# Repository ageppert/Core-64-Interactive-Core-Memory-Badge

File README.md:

# Core-64-Interactive-Core-Memory-Badge
Weave your own 64 bits of core memory over the top of LEDs to interact with directly using a magnetic wand.

Purchase: https://www.Core64.io

Follow this project at: https://hackaday.io/project/166155-core-64-interactive-core-memory-badge

You are in the development repository. Beta Kits and production version firmware is at https://github.com/ageppert/Core64/

# Hardware Version History (latest on top)

v0.5 Triple Board (added custom LED Matrix) - Beta Test Kits. Beta Kit Repo at https://github.com/ageppert/Core64/

v0.4 Core Board - Neon Pixel Edition. Expanded Core Grid Array to work with [Neon Pixels](https://pierremuth.wordpress.com/2020/07/08/neon-pixel/)!

v0.4 Dual Boards (Blue LB + Yellow CB), moved up to Teensy 3.2, removed IO Expanders, added more expansion/hacking headers.

v0.3.1 Hand re-worked v0.3 with 5V0 and 3V3 regulators each seperately sourced after power switch to provide improved power supplies.

v0.3 Dual Boards (both Red) with Teensy LC. One core board, one logic board. Used IO Expanders to drive the Core matrix, which ended up being way too slow.

v0.2 Bug fixes learned from v0.1 applied. This version has not been made or tested, but should work.

v0.1.1 Single Green Board worked after I added missing OR gate circuitry!

v0.1 Single Green Board with Teensy LC. The first hand assembled prototype. Made one and it worked after I added missing circuitry!

Share-A-Hack version

Proof-Of-Concept version

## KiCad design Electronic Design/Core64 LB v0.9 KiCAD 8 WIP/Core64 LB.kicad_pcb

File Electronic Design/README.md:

# Electronic Design

Datasheets

Native KiCad files for the schematic and PCB. (KiCad Version: (5.1.2-1)-1, release build)

Teensy LC Pin Usage Mapping

BOM

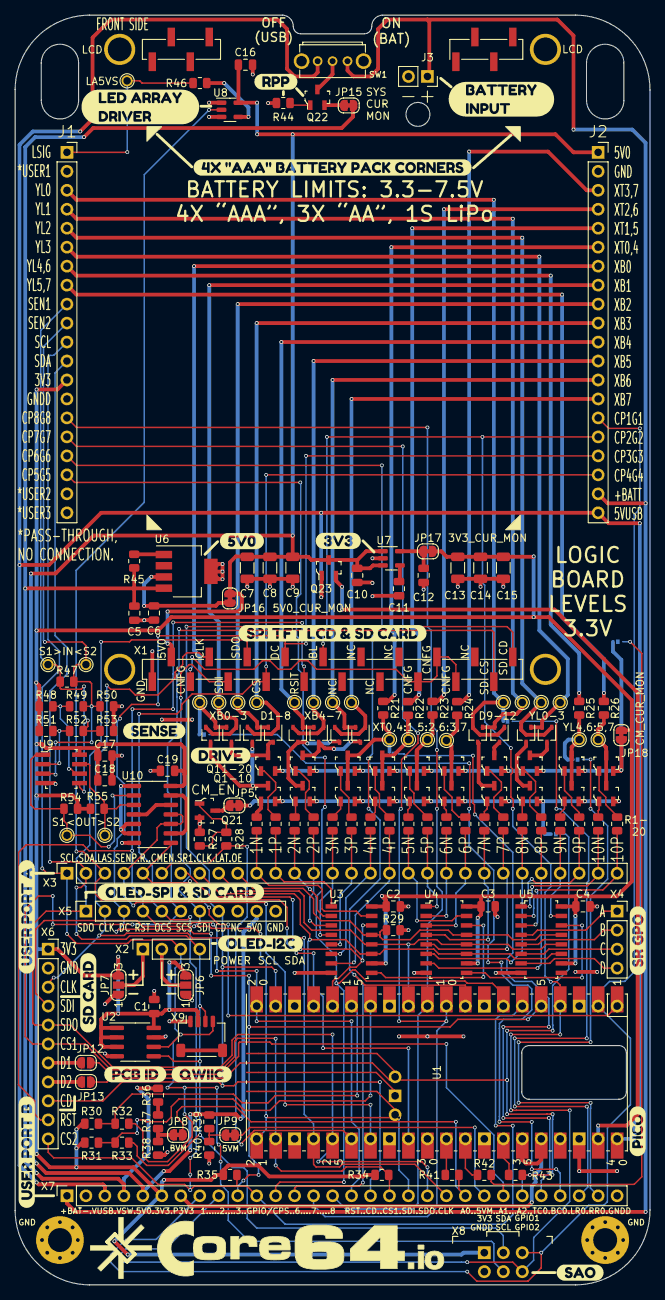
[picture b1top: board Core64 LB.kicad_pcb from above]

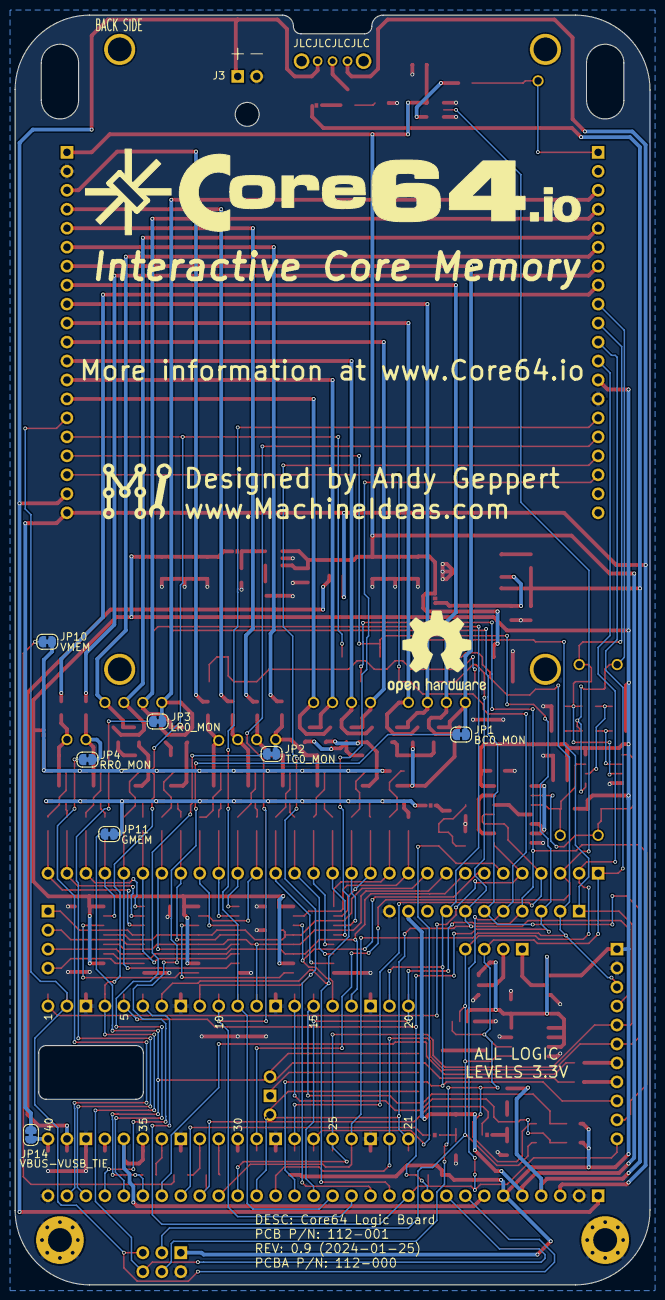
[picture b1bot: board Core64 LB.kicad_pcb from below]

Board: 2 copper layers, 85.0 x 170.0 mm, 198 parts (10 on the bottom side), 154 nets.

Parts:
C1, C2, C3, C4, C16, C17, C19: 0.1uF; C_0805_2012Metric
C5, C6, C10, C12: 1uF; C_0805_2012Metric
C7, C8, C9, C13, C14, C15: 220uF; C_1206_3216Metric
C11: 0.01uF; C_0805_2012Metric
C18: 10uF; C_0805_2012Metric
D1, D3, D5, D7, D9, D11: BAT54CW; SOT-323_SC-70
D2, D4, D6, D8, D10, D12: BAT54AW; SOT-323_SC-70
H1, H2: GND PAD; MountingHole_3.2mm_M3_Pad_Via
J1, J2: SSW-116-22-F-S-VS‎; PinSocket_1x20_P2.54mm_Vertical
J3: ALT. BATT.; PinSocket_1x02_P2.54mm_Vertical
JP1: BC0_MON; SolderJumper-2_P1.3mm_Bridged_RoundedPad1.0x1.5mm
JP2: TC0_MON; SolderJumper-2_P1.3mm_Bridged_RoundedPad1.0x1.5mm
JP3: LR0_MON; SolderJumper-2_P1.3mm_Bridged_RoundedPad1.0x1.5mm
JP4: RR0_MON; SolderJumper-2_P1.3mm_Bridged_RoundedPad1.0x1.5mm
JP5, JP11: GMEM; SolderJumper-2_P1.3mm_Bridged_RoundedPad1.0x1.5mm
JP6, JP7: SolderJumper_3_Open; SolderJumper-3_P1.3mm_Open_RoundedPad1.0x1.5mm_NumberLabels
JP8: BAT_MON; SolderJumper-2_P1.3mm_Bridged_RoundedPad1.0x1.5mm
JP9: 5V0_MON; SolderJumper-2_P1.3mm_Bridged_RoundedPad1.0x1.5mm
JP10: VMEM; SolderJumper-2_P1.3mm_Bridged_RoundedPad1.0x1.5mm
JP12: D1; SolderJumper-2_P1.3mm_Open_RoundedPad1.0x1.5mm
JP13: D2; SolderJumper-2_P1.3mm_Open_RoundedPad1.0x1.5mm
JP14: VBUS_VUSB_TIE; SolderJumper-2_P1.3mm_Bridged_RoundedPad1.0x1.5mm
JP15: SYS_CUR_MON; SolderJumper-2_P1.3mm_Bridged_RoundedPad1.0x1.5mm
JP16: 5V0_CUR_MON; SolderJumper-2_P1.3mm_Bridged_RoundedPad1.0x1.5mm
JP17: 3V3_CUR_MON; SolderJumper-2_P1.3mm_Bridged_RoundedPad1.0x1.5mm
JP18: CM_CUR_MON; SolderJumper-2_P1.3mm_Bridged_RoundedPad1.0x1.5mm
L1: Core_64_Logo; Core64.io_w_core_symbol
L1#2: Core_64_Logo; Machine_Ideas_logo_1
L2: Core_64_Logo; Core64.io_w_core_symbol2
L4: Logo_Open_Hardware_Small; OSHW-Logo2_14.6x12mm_SilkScreen
Q1, Q2, Q3, Q4, Q5, Q6, Q7, Q8, Q9, Q10: MMBT4401LT1G; SOT-23-3
Q11, Q12, Q13, Q14, Q15, Q16, Q17, Q18, Q19, Q20: MMBT4403LT1G; SOT-23-3
Q21: NVTR4503NT1G_NMOS_GSD; SOT-23-3
Q22, Q23: SL3401A; SOT-23-3
R1, R2, R3, R4, R5, R6, R7, R8, R9, R10, R11, R12, R13, R14, R15, R16, R17, R18, R19, R20, R28, R46: 470; R_0805_2012Metric
R21, R22, R23, R24, R25, R26: 6R8-5%; R_0805_2012Metric
R27, R29, R34, R35, R36, R37, R38, R39, R40, R44, R45: 10k; R_0805_2012Metric
R30, R31, R54, R55: 1K2; R_0805_2012Metric
R32, R33: 68; R_0805_2012Metric
R41, R42, R43: 1k2; R_0805_2012Metric
R47, R50, R53: 1K5-1%; R_0805_2012Metric
R48, R51: 1K8-1%; R_0805_2012Metric
R49, R52: 11-1%; R_0805_2012Metric
SW1: SK12D07L4B; SK12D07VG4
TP1: XB0; TestPoint_THTPad_D1.5mm_Drill1.0mm
TP2: XB1; TestPoint_THTPad_D1.5mm_Drill1.0mm
TP3: XB2; TestPoint_THTPad_D1.5mm_Drill1.0mm
TP4: XB3; TestPoint_THTPad_D1.5mm_Drill1.0mm
TP5: XB4; TestPoint_THTPad_D1.5mm_Drill1.0mm
TP6: XB5; TestPoint_THTPad_D1.5mm_Drill1.0mm
TP7: XB6; TestPoint_THTPad_D1.5mm_Drill1.0mm
TP8: XB7; TestPoint_THTPad_D1.5mm_Drill1.0mm
TP9: XT0,4; TestPoint_THTPad_D1.5mm_Drill1.0mm
TP10: XT1,5; TestPoint_THTPad_D1.5mm_Drill1.0mm
TP11: XT2,6; TestPoint_THTPad_D1.5mm_Drill1.0mm
TP12: XT3,7; TestPoint_THTPad_D1.5mm_Drill1.0mm
TP13: YL1; TestPoint_THTPad_D1.5mm_Drill1.0mm
TP14: YL0; TestPoint_THTPad_D1.5mm_Drill1.0mm
TP15: YL3; TestPoint_THTPad_D1.5mm_Drill1.0mm
TP16: YL2; TestPoint_THTPad_D1.5mm_Drill1.0mm
TP17: YL4,6; TestPoint_THTPad_D1.5mm_Drill1.0mm
TP18: YL5,7; TestPoint_THTPad_D1.5mm_Drill1.0mm
TP19: LA5VS; TestPoint_THTPad_D1.5mm_Drill1.0mm
TP20: S1 IN; TestPoint_THTPad_D1.5mm_Drill1.0mm
TP21: S2 IN; TestPoint_THTPad_D1.5mm_Drill1.0mm
TP22: S2 OUT; TestPoint_THTPad_D1.5mm_Drill1.0mm
TP23: S1 OUT; TestPoint_THTPad_D1.5mm_Drill1.0mm
U1: PICO; RPi_PicoW_SMD_TH_Abg
U2: M24C02-RMN; SOIC-8_3.9x4.9mm_P1.27mm
U3, U4, U5: 74HC595D; SOIC-16_W3.90mm
U6: LP38693MP-5.0; SOT-223-5
U7: SSP9193-33M5R; SOT-23-5
U8: SN74LV1T125DBVR; SOT-23-5
U9: LM393; SOIC-8_W3.9mm
U10: SN74HC02DR; SOIC-14_3.9x8.7mm_P1.27mm
X1: Adafruit_3.2_TFT_1743; Adafruit_3.2_TFT_Dual_PinHeader_1x20_P2.54mm_Vertical_SMD_P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
X2: SSW-104-22-L-S-VS; PinSocket_1x04_P2.54mm_Vertical
X3, X7: TBD; PinSocket_1x30_P2.54mm_Vertical
X4: CA_SR_GPO_ABCD; PinSocket_1x04_P2.54mm_Vertical
X5: HEADER_11-PIN_0.1; PinSocket_1x11_P2.54mm_Vertical
X6: Header_11-PIN_0.1; PinSocket_1x11_P2.54mm_Vertical
X8: SAO_conn_SFH11-NBPC-D03-ST-BK; Badgelife-SAOv169-BADGE-2x3
X9: QWIIC; JST_SH_SM04B-SRSS-TB_1x04-1MP_P1.00mm_Horizontal
kibuzzard-6417AF30: G***; kibuzzard-6417AF30
kibuzzard-6417CDFD: G***; kibuzzard-6417CDFD
kibuzzard-6417CE14: G***; kibuzzard-6417CE14
kibuzzard-64178C85: G***; kibuzzard-64178C85
kibuzzard-64178DD4: G***; kibuzzard-64178DD4
kibuzzard-64178DE8: G***; kibuzzard-64178DE8
kibuzzard-64178DF4: G***; kibuzzard-64178DF4
kibuzzard-64178E2E: G***; kibuzzard-64178E2E
kibuzzard-64178E4F: G***; kibuzzard-64178E4F
kibuzzard-64178E7C: G***; kibuzzard-64178E7C
kibuzzard-64178E9B: G***; kibuzzard-64178E9B
kibuzzard-64178E12: G***; kibuzzard-64178E12
kibuzzard-64178E45: G***; kibuzzard-64178E45
kibuzzard-64178E73: G***; kibuzzard-64178E73
kibuzzard-64178E92: G***; kibuzzard-64178E92
kibuzzard-64178EA5: G***; kibuzzard-64178EA5
kibuzzard-64179D69: G***; kibuzzard-64179D69
kibuzzard-64179D78: G***; kibuzzard-64179D78
kibuzzard-64179E5D: G***; kibuzzard-64179E5D

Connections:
3V3: C1.1, C2.1, C3.1, C4.1, C13.1, C14.1, C15.1, C17.1, C18.1, C19.1, J1.13, JP6.3 (B), JP7.3 (B), JP17.2 (B), JP18.1 (A), R30.1, R31.1, R34.1, R35.2, R48.1, R51.1, R54.1, R55.1, U2.1 (E0), U2.2 (E1), U2.3 (E2), U2.8 (VCC), U3.10 (~SRCLR), U3.16 (VCC), U4.10 (~SRCLR), U4.16 (VCC), U5.10 (~SRCLR), U5.16 (VCC), U9.8 (V+), U10.14 (VCC), X6.1, X7.6, X8.1 (3V3), X9.2
5V0: C7.1, C8.1, C9.1, C10.1, C16.1, J2.1, JP16.2 (B), Q23.3 (D), R39.1, U7.1 (IN), U7.3 (EN), U8.5 (VCC), X1.2 (3-5V), X5.10, X7.5
5VUSB: J2.20, JP14.2 (B), Q23.1 (G), SW1.3 (C), X7.3
+BATT: J2.19, J3.1, SW1.1 (A), X7.1
+VSW: C5.1, JP15.2 (B), R36.2, R45.1, U6.4 (IN), X7.4
-BATT: C1.2, C2.2, C3.2, C4.2, C5.2, C6.2, C7.2, C8.2, C9.2, C10.2, C11.2, C12.2, C13.2, C14.2, C15.2, C16.2, C17.2, C18.2, C19.2, H1.1, H2.1, J1.14, J2.2, J3.2, JP6.1 (A), JP7.1 (A), Q21.2 (S), R27.1, R29.1, R38.2, R40.2, R44.2, R50.2, R53.2, U1.3 (GND), U1.8 (GND), U1.13 (GND), U1.18 (GND), U1.23 (GND), U1.28 (GND), U1.33 (AGND/GND), U1.38 (GND), U2.4 (VSS), U2.7 (~WC), U3.8 (GND), U4.8 (GND), U5.8 (GND), U6.5 (GND), U7.2 (GND), U8.1 (/OE), U8.3 (GND), U9.4 (V-), U10.7 (GND), X1.1 (GND), X5.11, X6.2, X7.2, X7.30, X8.2 (GND), X9.1
/ADC0: R41.1, U1.31 (I2C1_SDA/ADC0/GP26)
/ADC0_BUFF: JP8.2 (B), R41.2, X7.22
/ADC1: R42.1, U1.32 (I2C1_SCL/ADC1/GP27)
/ADC1_BUFF: JP10.1 (A), JP12.2 (B), R42.2, X7.24
/ADC2: R43.1, U1.34 (ADC2/GP28)
/ADC2_BUFF: JP11.1 (A), JP13.2 (B), R43.2, X7.25
/CA_SENSE_1_OUT: R55.2, TP23.1, U9.7, U10.3
/CA_SENSE_2_OUT: R54.2, TP22.1, U9.1, U10.2
/CA_SR_GPO_A: U5.4 (QE), X4.1
/CA_SR_GPO_B: U5.5 (QF), X4.2
/CA_SR_GPO_C: U5.6 (QG), X4.3
/CA_SR_GPO_D: U5.7 (QH), X4.4
/CA_SR_SER2: U3.9 (QH'), U4.14 (SER)
/CA_SR_SER3: U4.9 (QH'), U5.14 (SER)
/CM_EN: R28.1, U1.26 (I2C0_SDA/GP20), X3.6
/CM_Q1N: R1.2, U3.15 (QA), X3.11
/CM_Q1P: R2.2, U3.1 (QB), X3.12
/CM_Q2N: R3.2, U3.2 (QC), X3.13
/CM_Q2P: R4.2, U3.3 (QD), X3.14
/CM_Q3N: R5.2, U3.4 (QE), X3.15
/CM_Q3P: R6.2, U3.5 (QF), X3.16
/CM_Q4N: R7.2, U3.6 (QG), X3.17
/CM_Q4P: R8.2, U3.7 (QH), X3.18
/CM_Q5N: R9.2, U4.15 (QA), X3.19
/CM_Q5P: R10.2, U4.1 (QB), X3.20
/CM_Q6N: R11.2, U4.2 (QC), X3.21
/CM_Q6P: R12.2, U4.3 (QD), X3.22
/CM_Q7N: R13.2, U4.4 (QE), X3.23
/CM_Q7P: R14.2, U4.5 (QF), X3.24
/CM_Q8N: R15.2, U4.6 (QG), X3.25
/CM_Q8P: R16.2, U4.7 (QH), X3.26
/CM_Q9N: R17.2, U5.15 (QA), X3.27
/CM_Q9P: R18.2, U5.1 (QB), X3.28
/CM_Q10N: R19.2, U5.2 (QC), X3.29
/CM_Q10P: R20.2, U5.3 (QD), X3.30
/CM_SENSE_1_IN: J1.9, R47.1, R52.2, R53.1, TP20.1, U9.5 (+)
/CM_SENSE_2_IN: J1.10, R47.2, R49.2, R50.1, TP21.1, U9.3 (+)
/CM_SENSE_PULSE: U1.27 (I2C0_SCL/GP21), U10.10, U10.11, X3.4
/CM_SENSE_RESET: U1.1 (UART0_TX/I2C0_SDA/SPI0_RX/GP0), U10.8, X3.5
/CM_SR_CLK: U1.17 (UART0_RX/I2C0_SCL/SPI1_CSn/GP13), U3.11 (SRCLK), U4.11 (SRCLK), U5.11 (SRCLK), X3.8
/CM_SR_LAT: U1.12 (UART1_RX/I2C0_SCL/SPI1_CSn/GP9), U3.12 (RCLK), U4.12 (RCLK), U5.12 (RCLK), X3.9
/CM_SR_SER1: U1.16 (UART0_TX/I2C0_SDA/GPI1_RX/GP12), U3.14 (SER), X3.7
/CM_SR_~OE: R29.2, U3.13 (~OE), U4.13 (~OE), U5.13 (~OE), X3.10
/GPIO1_CP1_SAO1: J2.15, U1.2 (UART0_RX/I2C0_SCL/GPI0_CSn/GP1), X7.8, X8.5 (GPIO1)
/GPIO2_CP2_SAO2: J2.16, U1.4 (I2C1_SDA/SPI0_SCK/GP2), X1.10 (LITE), X7.9, X8.6 (GPIO2)
/GPIO3_CP3_DC: J2.17, U1.5 (I2C1_SCL/SPI0_TX/GP3), X1.8 (D/C), X5.3, X7.10
/GPIO4_CP4_CS2: J2.18, R35.1, U1.6 (UART1_TX/I2C0_SDA/SPI0_RX/GP4), X1.7 (CS), X5.5, X6.11, X7.11
/GPIO5_CP5_HS1: J1.18, U1.7 (UART1_RX/I2C0_SCL/SPI0_CSn/GP5), X7.12
/GPIO6_CP6_HS2: J1.17, U1.9 (I2C1_SDA/SPI0_SCK/GP6), X7.13
/GPIO7_CP7_HS3: J1.16, U1.10 (I2C1_SCL/SPI0_TX/GP7), X7.14
/GPIO8_CP8_HS4: J1.15, U1.11 (UART1_TX/I2C0_SDA/SPI1_RX/GP8), X7.15
/I2C_3V3_SCL: J1.11, R32.2, U2.6 (SCL), X2.3, X3.1, X8.4 (SCL), X9.4
/I2C_3V3_SDA: J1.12, R33.1, U2.5 (SDA), X2.4, X3.2, X8.3 (SDA), X9.3
/I2C_CLOCK: R30.2, R32.1, U1.15 (I2C1_SCL/SPI1_TX/GP11)
/I2C_DATA: R31.2, R33.2, U1.14 (I2C1_SDA/SPI1_SCK/GP10)
/LED_ARY_3V3_SIG: U1.29 (GP22), U8.2 (A), X3.3
/LED_ARY_5V0_SIG: J1.1, R46.1, TP19.1
/QSPI_D1: JP12.1 (A), X6.7
/QSPI_D2: JP13.1 (A), X6.8
/SPI_CD: U1.19 (I2C1_SDA/SPI1_SCK/GP14), X1.20 (Card_Det.), X5.8, X6.9, X7.17
/SPI_CLK: U1.24 (I2C1_SDA/SPI0_SCK/GP18), X1.4 (CLK), X5.2, X6.3, X7.21
/SPI_CS1: R34.2, U1.22 (UART0_RX/I2C0_SCL/SPI0_CSn/GP17), X1.19 (Card_CS), X5.6, X6.6, X7.18
/SPI_RESET: U1.20 (I2C1_SCL/SPI1_TX/GP15), X1.9 (RST), X5.4, X6.10, X7.16
/SPI_SDI: U1.21 (UART0_TX/I2C0_SDA/SPI0_RX/GP16), X1.5 (MISO), X5.7, X6.4, X7.19
/SPI_SDO: U1.25 (I2C1_SCL/SPI0_TX/GP19), X1.6 (MOSI), X5.1, X6.5, X7.20
/XB0: D1.1, D2.2, J2.7, JP1.2 (B), TP1.1
/XB1: D1.2, D2.1, J2.8, TP2.1
/XB2: D3.1, D4.2, J2.9, TP3.1
/XB3: D3.2, D4.1, J2.10, TP4.1
/XB4: D5.1, D6.2, J2.11, TP5.1
/XB5: D5.2, D6.1, J2.12, TP6.1
/XB6: D7.1, D8.2, J2.13, TP7.1
/XB7: D7.2, D8.1, J2.14, TP8.1
/XT0,4: J2.6, R21.2
/XT1,5: J2.5, R22.1
/XT2,6: J2.4, R23.1
/XT3,7: J2.3, R24.1
/YL0: D9.2, D10.1, J1.3, JP3.2 (B), TP14.1
/YL1: D9.1, D10.2, J1.4, TP13.1
/YL2: D11.2, D12.1, J1.5, TP16.1
/YL3: D11.1, D12.2, J1.6, TP15.1
/YL4,6: J1.7, R25.1
/YL5,7: J1.8, R26.1
BC0_MON: JP1.1 (A), X7.27
GMEM: JP5.2 (B), JP11.2 (B), Q1.2 (E), Q2.2 (E), Q3.2 (E), Q4.2 (E), Q5.2 (E), Q6.2 (E), Q7.2 (E), Q8.2 (E), Q9.2 (E), Q10.2 (E)
LR0_MON: JP3.1 (A), X7.28
unnamed: JP2.2 (B), Q3.3 (C), Q13.3 (C), R21.1, TP9.1
unnamed: JP4.2 (B), Q9.3 (C), Q19.3 (C), R25.2, TP17.1
unnamed: JP5.1 (A), Q21.3 (D)
unnamed: JP6.2 (C), X2.2
unnamed: JP7.2 (C), X2.1
unnamed: JP8.1 (A), R37.1, R38.1
unnamed: JP9.1 (A), X7.23
unnamed: JP9.2 (B), R39.2, R40.1
unnamed: JP15.1 (A), Q22.2 (S)
unnamed: C6.1, JP16.1 (A), U6.3 (VOUT)
unnamed: C12.1, JP17.1 (A), U7.5 (OUT)
unnamed: Q1.1 (B), R1.1
unnamed: D1.3, D3.3, Q1.3 (C)
unnamed: Q2.1 (B), R3.1
unnamed: D5.3, D7.3, Q2.3 (C)
unnamed: Q3.1 (B), R5.1
unnamed: Q4.1 (B), R7.1
unnamed: Q5.1 (B), R9.1
unnamed: Q6.1 (B), R11.1
unnamed: Q7.1 (B), R13.1
unnamed: D9.3, Q7.3 (C)
unnamed: Q8.1 (B), R15.1
unnamed: D11.3, Q8.3 (C)
unnamed: Q9.1 (B), R17.1
unnamed: Q10.1 (B), R19.1
unnamed: Q10.3 (C), Q20.3 (C), R26.2, TP18.1
unnamed: Q11.1 (B), R2.1
unnamed: D2.3, D4.3, Q11.3 (C)
unnamed: Q12.1 (B), R4.1
unnamed: D6.3, D8.3, Q12.3 (C)
unnamed: Q13.1 (B), R6.1
unnamed: Q14.1 (B), R8.1
unnamed: Q4.3 (C), Q14.3 (C), R22.2, TP10.1
unnamed: Q15.1 (B), R10.1
unnamed: Q5.3 (C), Q15.3 (C), R23.2, TP11.1
unnamed: Q16.1 (B), R12.1
unnamed: Q6.3 (C), Q16.3 (C), R24.2, TP12.1
unnamed: Q17.1 (B), R14.1
unnamed: D10.3, Q17.3 (C)
unnamed: Q18.1 (B), R16.1
unnamed: D12.3, Q18.3 (C)
unnamed: Q19.1 (B), R18.1
unnamed: Q20.1 (B), R20.1
unnamed: Q21.1 (G), R27.2, R28.2
unnamed: Q22.3 (D), SW1.2 (B)
unnamed: Q22.1 (G), R44.1
unnamed: R36.1, R37.2
unnamed: R45.2, U6.1 (EN)
unnamed: C11.1, U7.4 (BP)
unnamed: R46.2, U8.4 (Y)
unnamed: R51.2, R52.1, U9.2 (-)
unnamed: R48.2, R49.1, U9.6 (_)
unnamed: U10.1, U10.5, U10.6
unnamed: U10.4, U10.12
unnamed: U10.9, U10.13
unnamed: X1.3 (3.3V), X1.15 (IM3), X1.16 (IM2), X1.17 (IM1)
PICO_3V3OUT: U1.35 (ADC_VREF), U1.36 (3V3OUT), X7.7
PICO_VBUS: JP14.1 (A), U1.40 (VBUS)
PICO_VSYS: Q23.2 (S), U1.39 (VSYS)
RR0_MON: JP4.1 (A), X7.29
TC0_MON: JP2.1 (A), X7.26
VMEM: JP10.2 (B), JP18.2 (B), Q11.2 (E), Q12.2 (E), Q13.2 (E), Q14.2 (E), Q15.2 (E), Q16.2 (E), Q17.2 (E), Q18.2 (E), Q19.2 (E), Q20.2 (E)

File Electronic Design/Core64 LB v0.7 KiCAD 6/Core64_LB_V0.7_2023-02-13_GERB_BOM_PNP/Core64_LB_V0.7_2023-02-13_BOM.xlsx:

Comment | Designator | Footprint | LCSC Part Number
0.1uF | C1,C2,C3,C4, C16, C17, C19 | Capacitor_SMD:C_0805_2012Metric | C28233
1uF | C5, C6, C10, C12 | Capacitor_SMD:C_0805_2012Metric | C28323
220uF | C7, C8, C9, C13, C14, C15 | Capacitor_SMD:C_1206_3216Metric | C412252
0.01uF | C11 | Capacitor_SMD:C_0805_2012Metric | C1710
10uF | C18 | Capacitor_SMD:C_0805_2012Metric | C17024
BAT54AW | D2, D4, D6, D8, D10, D12 | Package_TO_SOT_SMD:SOT-323_SC-70 | C78261
BAT54CW | D1, D3, D5, D7, D9, D11 | Package_TO_SOT_SMD:SOT-323_SC-70 | C83573
MMBT4401LT1G | Q1, Q2, Q3, Q4, Q5, Q6, Q7, Q8, Q9, Q10 | digikey-kicad-library-master:SOT-23-3 | C31776
MMBT4403LT1G | Q11, Q12, Q13, Q14, Q15, Q16, Q17, Q18, Q19, Q20 | digikey-kicad-library-master:SOT-23-3 | C78864
NVTR4503NT1G_NMOS_GSD | Q21 | digikey-kicad-library-master:SOT-23-3 | C20917
SL3401A | Q22, Q23 | digikey-kicad-library-master:SOT-23-3 | C350311
6R8-5% | R21, R22, R23, R24, R25, R26 | Resistor_SMD:R_0805_2012Metric | C17774
470 | R1, R2, R3, R4, R5, R6, R7, R8, R9, R10, R11, R12, R13, R14, R15, R16, R17, R18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 | Resistor_SMD:R_0805_2012Metric | C17710
1K2 | R30, R31, R54, R55 | Resistor_SMD:R_0805_2012Metric | C17379
68 | R32, R33 | Resistor_SMD:R_0805_2012Metric | C17802
10k | R27, R29, R34, R35, R36, R37, R38, R39, R40, R44, R45 | Resistor_SMD:R_0805_2012Metric | C17414
1k2 | R41, R42, R43 | Resistor_SMD:R_0805_2012Metric | C17379
1K5-1% | R47, R50, R53 | Resistor_SMD:R_0805_2012Metric | C4310
1K8-1% | R48, R51 | Resistor_SMD:R_0805_2012Metric | C17398
11-1% | R49, R52 | Resistor_SMD:R_0805_2012Metric | C17430
SK12D07L4B | SW1 | Switch_XKB_SK12D07VG4_SK12D07L4B:SK12D07VG4 | C480340
M24C02-RMN | U2 | Package_SO:SOIC-8_3.9x4.9mm_P1.27mm | C7562
74HC595D | U3, U4, U5 | digikey-kicad-library-master:SOIC-16_W3.90mm | C5947
LP38693MP-5.0 | U6 | Package_TO_SOT_SMD:SOT-223-5 | C140294
SSP9193-33M5R | U7 | Package_TO_SOT_SMD:SOT-23-5 | C411022
SN74LV1T125DBVR | U8 | Package_TO_SOT_SMD:SOT-23-5 | C473338
LM393 | U9 | digikey-kicad-library-master:SOIC-8_W3.9mm | C7955
SN74HC02DR | U10 | Package_SO:SOIC-14_3.9x8.7mm_P1.27mm | C350559
QWIIC | X9 | Connector_JST:JST_SH_SM04B-SRSS-TB_1x04-1MP_P1.00mm_Horizontal | C160404

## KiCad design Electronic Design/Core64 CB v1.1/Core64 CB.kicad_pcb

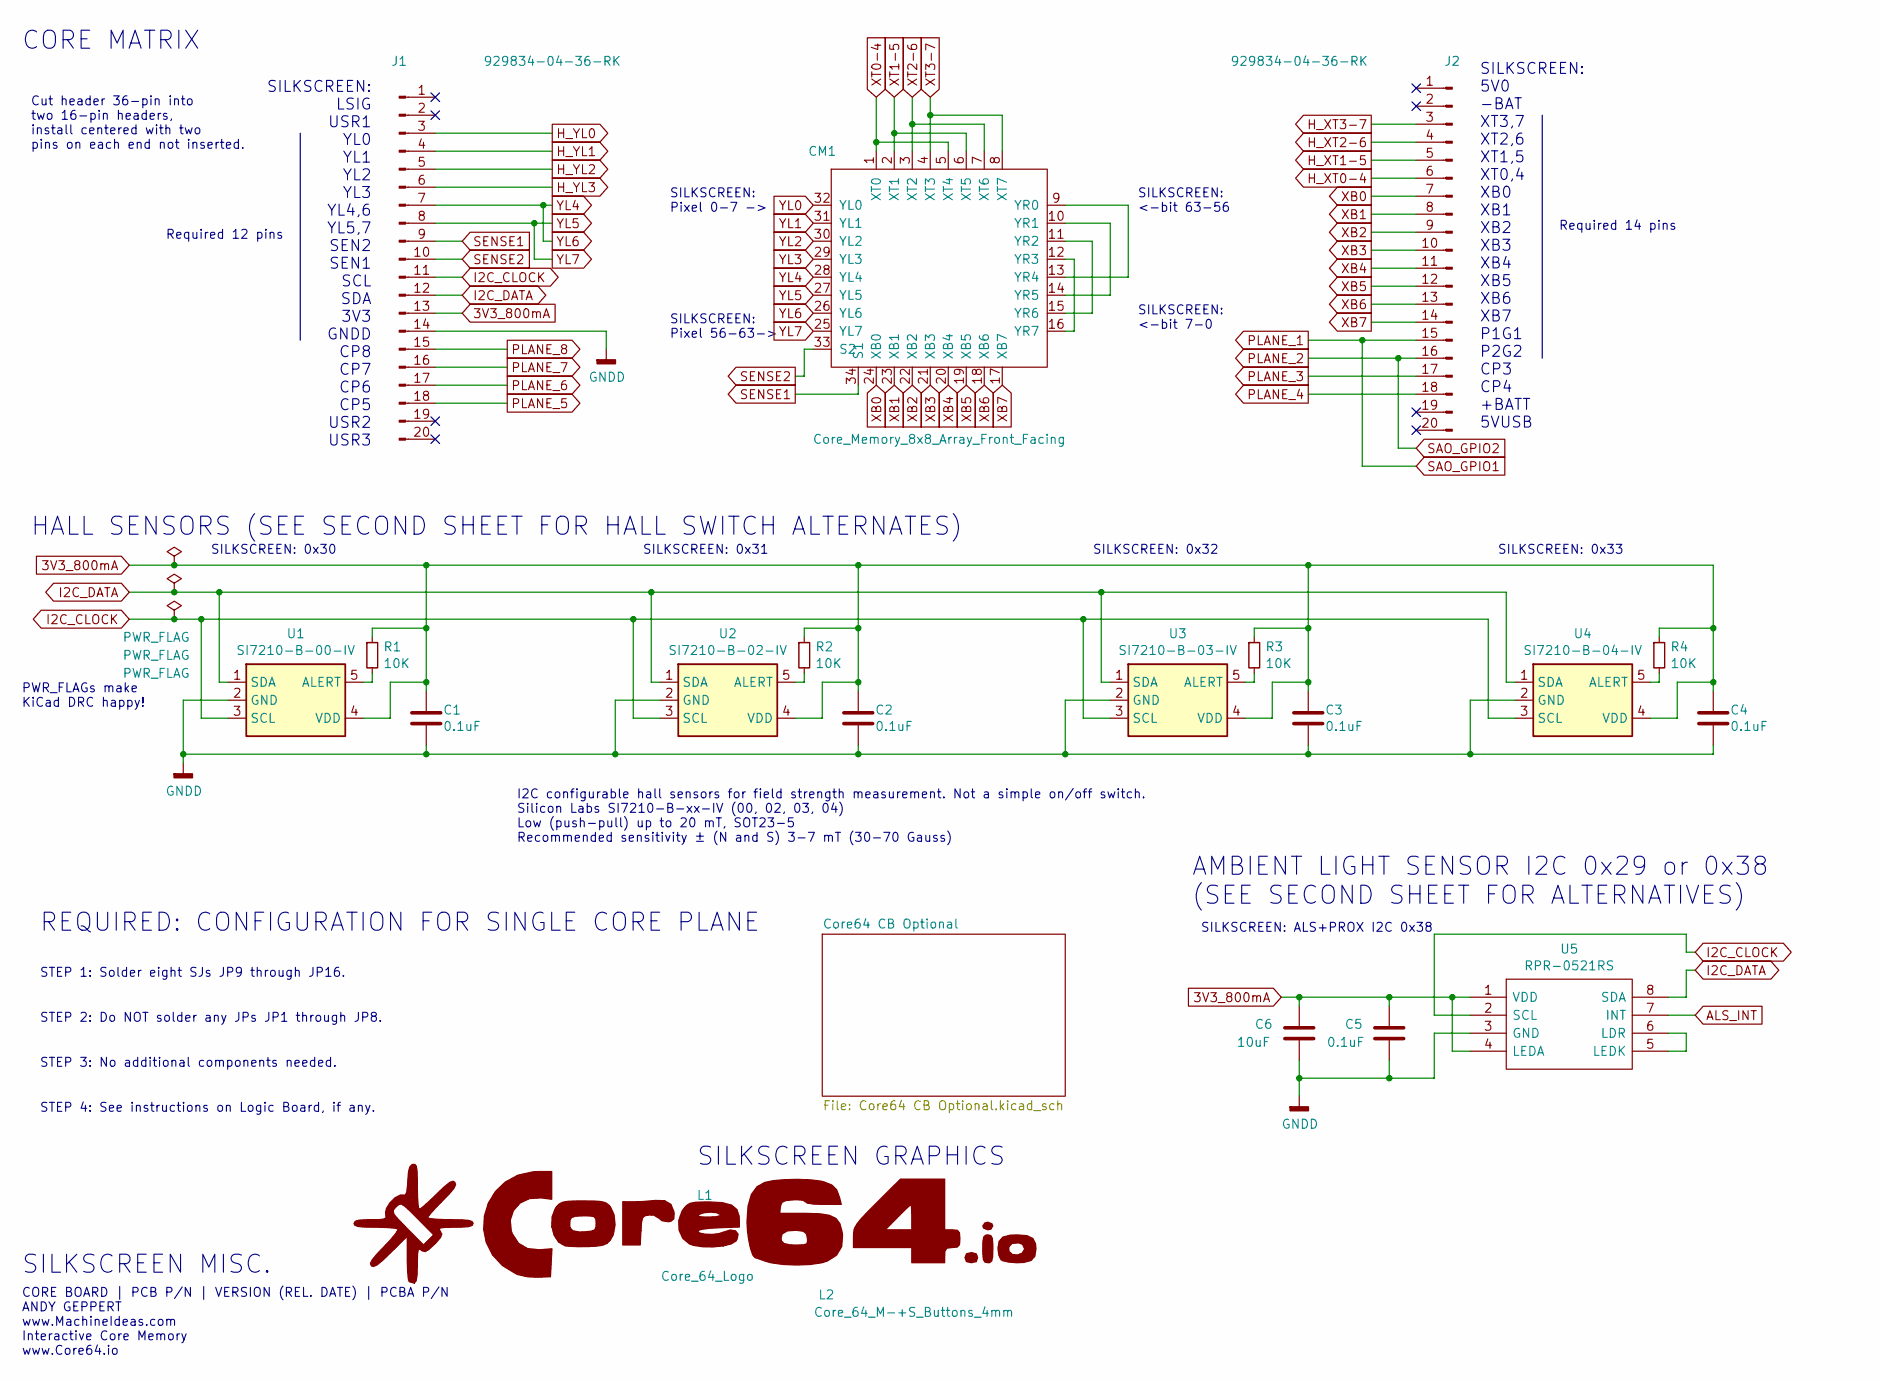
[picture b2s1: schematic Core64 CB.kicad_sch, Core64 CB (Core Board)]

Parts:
C1, C2, C3, C4, C5: 0.1uF; C_0805_2012Metric; LCSC C396718
C6: 10uF; C_0805_2012Metric; LCSC C396718
CM1: Core_Memory_8x8_Array_Front_Facing; core_64_6.75mm_square_v0.5_front_facing
J1, J2: 929834-04-36-RK; PinHeader_1x20_P2.54mm_Vertical_SMD_and_TH_Pin1Right; Mfg P/N 929834-04-36-RK
L1: Core_64_Logo; Core64.io_w_core_symbol_9mm_tall
L2: Core_64_M-+S_Buttons_4mm; Core64-M_-_+_S_Buttons
R1, R2, R3, R4: 10K; R_0805_2012Metric; LCSC C269724
U1: SI7210-B-00-IV; SOT-23-5; Mfg P/N SI7210-B-00-IV
U2: SI7210-B-02-IV; SOT-23-5; Mfg P/N SI7210-B-02-IV
U3: SI7210-B-03-IV; SOT-23-5; Mfg P/N SI7210-B-03-IV
U4: SI7210-B-04-IV; SOT-23-5; Mfg P/N SI7210-B-04-IV
U5: RPR-0521RS; RPR0521RS; Manufacturer_Part_Number RPR-0521RS; Mouser Part Number 755-RPR-0521RS

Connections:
3V3_800mA: C1.1, C2.1, C3.1, C4.1, C5.1, C6.1, J1.13, R1.1, R2.1, R3.1, R4.1, U1.4 (VDD), U2.4 (VDD), U3.4 (VDD), U4.4 (VDD), U5.1 (VDD), U5.4 (LEDA); also elsewhere on the board
ALS_INT: U5.7 (INT); also elsewhere on the board
GNDD: C1.2, C2.2, C3.2, C4.2, C5.2, C6.2, J1.14, U1.2 (GND), U2.2 (GND), U3.2 (GND), U4.2 (GND), U5.3 (GND); also elsewhere on the board
H_XT0-4: J2.6; also elsewhere on the board
H_XT1-5: J2.5; also elsewhere on the board
H_XT2-6: J2.4; also elsewhere on the board
H_XT3-7: J2.3; also elsewhere on the board
H_YL0: J1.3; also elsewhere on the board
H_YL1: J1.4; also elsewhere on the board
H_YL2: J1.5; also elsewhere on the board
H_YL3: J1.6; also elsewhere on the board
I2C_CLOCK: J1.11, U1.3 (SCL), U2.3 (SCL), U3.3 (SCL), U4.3 (SCL), U5.2 (SCL); also elsewhere on the board
I2C_DATA: J1.12, U1.1 (SDA), U2.1 (SDA), U3.1 (SDA), U4.1 (SDA), U5.8 (SDA); also elsewhere on the board
unnamed: CM1.9 (YR0), CM1.13 (YR4)
unnamed: CM1.10 (YR1), CM1.14 (YR5)
unnamed: CM1.11 (YR2), CM1.15 (YR6)
unnamed: CM1.12 (YR3), CM1.16 (YR7)
unnamed: R1.2, U1.5 (ALERT)
unnamed: R2.2, U2.5 (ALERT)
unnamed: R3.2, U3.5 (ALERT)
unnamed: R4.2, U4.5 (ALERT)
unnamed: U5.5 (LEDK), U5.6 (LDR)
PLANE_1: J2.15; also elsewhere on the board
PLANE_2: J2.16; also elsewhere on the board
PLANE_3: J2.17; also elsewhere on the board
PLANE_4: J2.18; also elsewhere on the board
PLANE_5: J1.18; also elsewhere on the board
PLANE_6: J1.17; also elsewhere on the board
PLANE_7: J1.16; also elsewhere on the board
PLANE_8: J1.15; also elsewhere on the board
SENSE1: CM1.34 (S1), J1.9
SENSE2: CM1.33 (S2), J1.10
XB0: CM1.24 (XB0), J2.7
XB1: CM1.23 (XB1), J2.8
XB2: CM1.22 (XB2), J2.9
XB3: CM1.21 (XB3), J2.10
XB4: CM1.20 (XB4), J2.11
XB5: CM1.19 (XB5), J2.12
XB6: CM1.18 (XB6), J2.13
XB7: CM1.17 (XB7), J2.14
XT0-4: CM1.1 (XT0), CM1.5 (XT4); also elsewhere on the board
XT1-5: CM1.2 (XT1), CM1.6 (XT5); also elsewhere on the board
XT2-6: CM1.3 (XT2), CM1.7 (XT6); also elsewhere on the board
XT3-7: CM1.4 (XT3), CM1.8 (XT7); also elsewhere on the board
YL0: CM1.32 (YL0); also elsewhere on the board
YL1: CM1.31 (YL1); also elsewhere on the board
YL2: CM1.30 (YL2); also elsewhere on the board
YL3: CM1.29 (YL3); also elsewhere on the board
YL4: CM1.26 (YL6), CM1.28 (YL4), J1.7
YL5: CM1.25 (YL7), CM1.27 (YL5), J1.8

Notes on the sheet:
SILKSCREEN MISC.
SILKSCREEN: 0x33
SILKSCREEN: <-bit 7-0
AMBIENT LIGHT SENSOR I2C 0x29 or 0x38 (SEE SECOND SHEET FOR ALTERNATIVES)
SILKSCREEN: ALS+PROX I2C 0x38
SILKSCREEN GRAPHICS
REQUIRED: CONFIGURATION FOR SINGLE CORE PLANE
SILKSCREEN: <-bit 63-56
PWR_FLAGs make KiCad DRC happy!
STEP 4: See instructions on Logic Board, if any.
SILKSCREEN: Pixel 0-7 ->
Cut header 36-pin into two 16-pin headers, install centered with two pins on each end not inserted.
SILKSCREEN: LSIG USR1 YL0 YL1 YL2 YL3 YL4,6 YL5,7 SEN2 SEN1 SCL SDA 3V3 GNDD CP8 CP7 CP6 CP5 USR2 USR3
SILKSCREEN: Pixel 56-63->
STEP 1: Solder eight SJs JP9 through JP16.
I2C configurable hall sensors for field strength measurement. Not a simple on/off switch. Silicon Labs SI7210-B-xx-IV (00, 02, 03, 04) Low (push-pull) up to 20 mT, SOT23-5 Recommended sensitivity ± (N and S) 3-7 mT (30-70 Gauss)
SILKSCREEN: 5V0 -BAT XT3,7 XT2,6 XT1,5 XT0,4 XB0 XB1 XB2 XB3 XB4 XB5 XB6 XB7 P1G1 P2G2 CP3 CP4 +BATT 5VUSB
CORE MATRIX
HALL SENSORS (SEE SECOND SHEET FOR HALL SWITCH ALTERNATES)
Required 12 pins
SILKSCREEN: 0x32
STEP 2: Do NOT solder any JPs JP1 through JP8.
SILKSCREEN: 0x30
CORE BOARD | PCB P/N | VERSION (REL. DATE) | PCBA P/N ANDY GEPPERT www.MachineIdeas.com Interactive Core Memory www.Core64.io
SILKSCREEN: 0x31
STEP 3: No additional components needed.
Required 14 pins

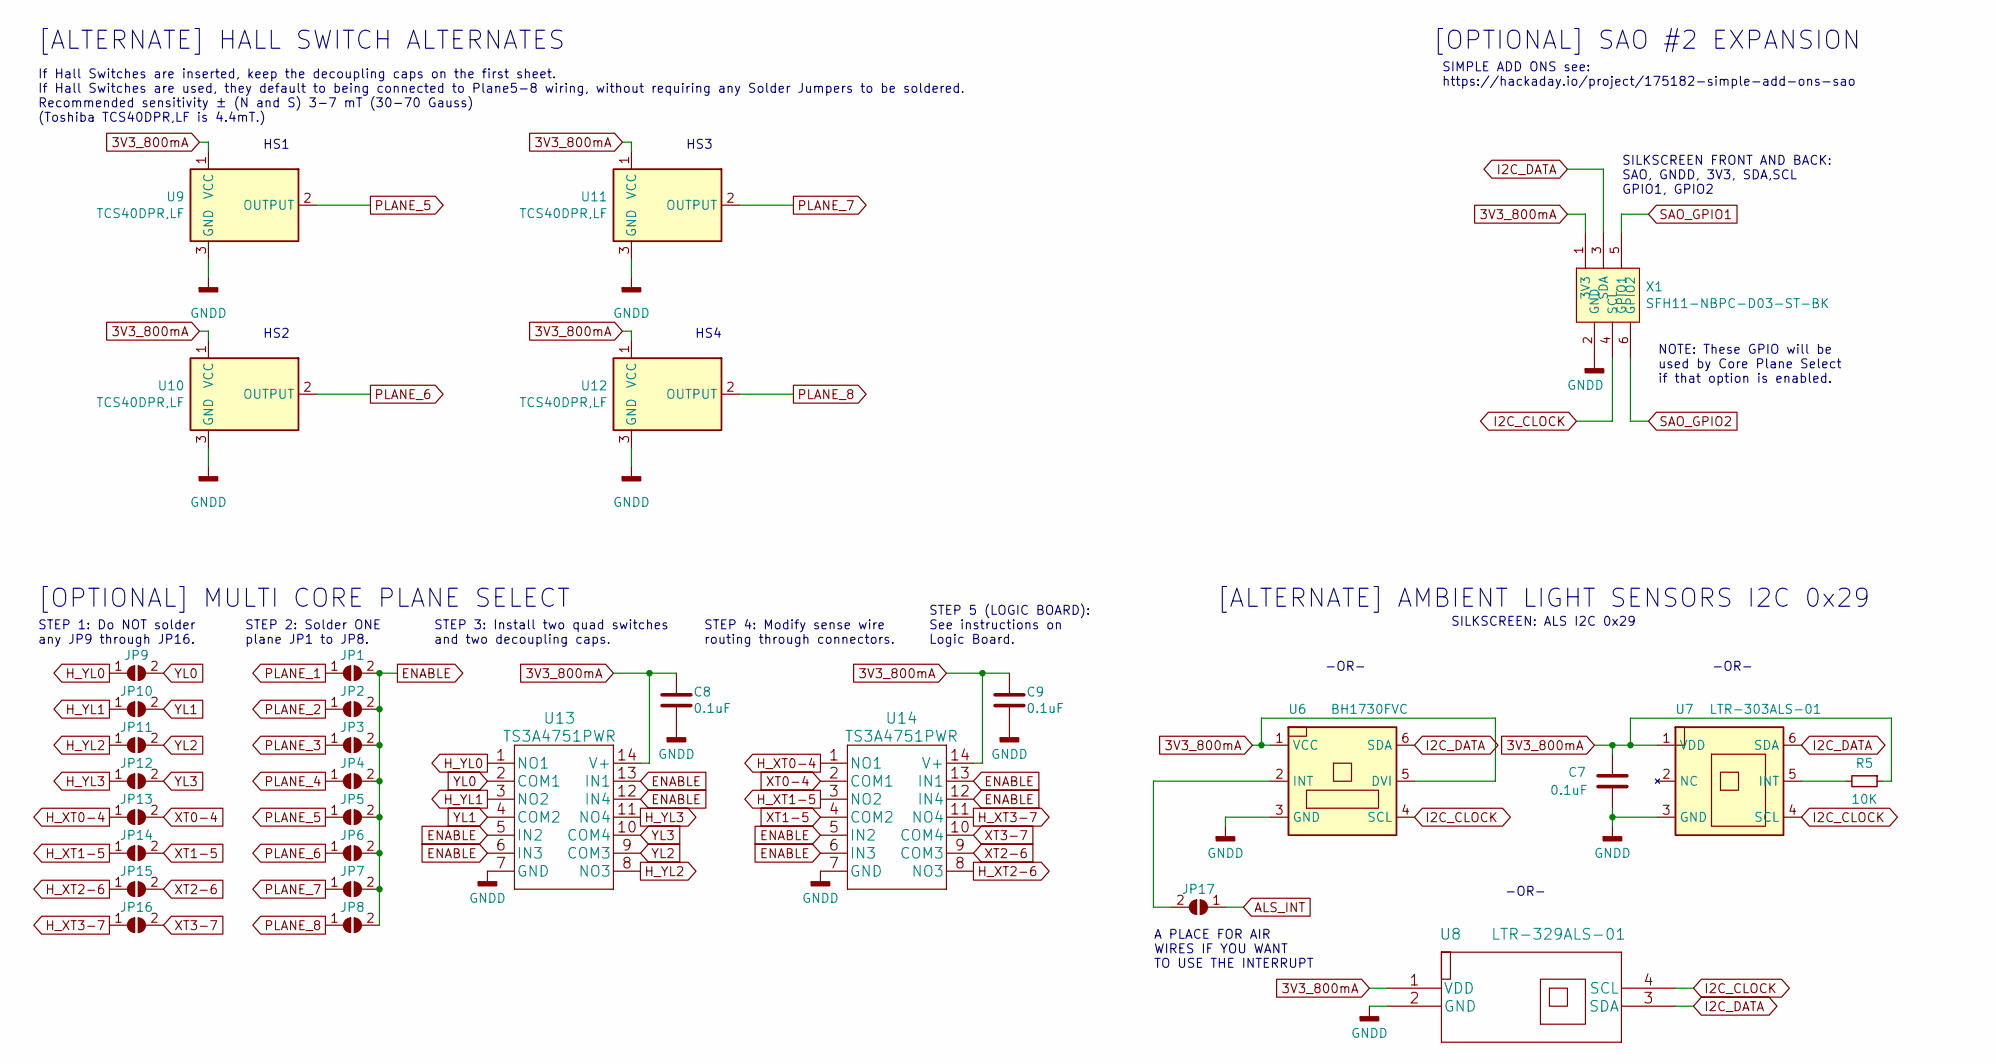
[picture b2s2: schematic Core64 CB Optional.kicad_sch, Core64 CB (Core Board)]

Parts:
C7, C8, C9: 0.1uF; C_0805_2012Metric
JP1, JP2, JP3, JP4, JP5, JP6, JP7, JP8, JP9, JP10, JP11, JP12, JP13, JP14, JP15, JP16, JP17: SolderJumper_2_Open; SolderJumper-2_P1.3mm_Open_Pad1.0x1.5mm
R5: 10K; R_0805_2012Metric; LCSC C269724
U6: BH1730FVC; REG_BD00IC0WHFV-GTR; Mfg P/N BH1730FVC-TR
U7: LTR-303ALS-01; Lite-On_LTR-303ALS-01; Mfg P/N LTR-303ALS-01; LCSC C364577
U8: LTR-329ALS-01; Mfg P/N LTR-329ALS-01
U9, U10, U11, U12: TCS40DPR,LF; SOT-23
U13, U14: TS3A4751PWR; Mfg P/N TS3A4751PWR
X1: SFH11-NBPC-D03-ST-BK; Badgelife-SAOv169-BADGE-2x3

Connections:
3V3_800mA: C7.1, C8.1, C9.1, R5.1, U6.1 (VCC), U6.5 (DVI), U7.1 (VDD), U8.1 (VDD), U9.1 (VCC), U10.1 (VCC), U11.1 (VCC), U12.1 (VCC), U13.14 (V+), U14.14 (V+), X1.1 (3V3); also elsewhere on the board
ALS_INT: JP17.1 (A); also elsewhere on the board
ENABLE: JP1.2 (B), JP2.2 (B), JP3.2 (B), JP4.2 (B), JP5.2 (B), JP6.2 (B), JP7.2 (B), JP8.2 (B), U13.5 (IN2), U13.6 (IN3), U13.12 (IN4), U13.13 (IN1), U14.5 (IN2), U14.6 (IN3), U14.12 (IN4), U14.13 (IN1)
GNDD: C7.2, C8.2, C9.2, U6.3 (GND), U7.3 (GND), U8.2 (GND), U9.3 (GND), U10.3 (GND), U11.3 (GND), U12.3 (GND), U13.7 (GND), U14.7 (GND), X1.2 (GND); also elsewhere on the board
H_XT0-4: JP13.1 (A), U14.1 (NO1); also elsewhere on the board
H_XT1-5: JP14.1 (A), U14.3 (NO2); also elsewhere on the board
H_XT2-6: JP15.1 (A), U14.8 (NO3); also elsewhere on the board
H_XT3-7: JP16.1 (A), U14.11 (NO4); also elsewhere on the board
H_YL0: JP9.1 (A), U13.1 (NO1); also elsewhere on the board
H_YL1: JP10.1 (A), U13.3 (NO2); also elsewhere on the board
H_YL2: JP11.1 (A), U13.8 (NO3); also elsewhere on the board
H_YL3: JP12.1 (A), U13.11 (NO4); also elsewhere on the board
I2C_CLOCK: U6.4 (SCL), U7.4 (SCL), U8.4 (SCL), X1.4 (SCL); also elsewhere on the board
I2C_DATA: U6.6 (SDA), U7.6 (SDA), U8.3 (SDA), X1.3 (SDA); also elsewhere on the board
unnamed: JP17.2 (B), U6.2 (INT)
unnamed: R5.2, U7.5 (INT)
PLANE_1: JP1.1 (A), X1.5 (GPIO1); also elsewhere on the board
PLANE_2: JP2.1 (A), X1.6 (GPIO2); also elsewhere on the board
PLANE_3: JP3.1 (A); also elsewhere on the board
PLANE_4: JP4.1 (A); also elsewhere on the board
PLANE_5: JP5.1 (A), U9.2 (OUTPUT); also elsewhere on the board
PLANE_6: JP6.1 (A), U10.2 (OUTPUT); also elsewhere on the board
PLANE_7: JP7.1 (A), U11.2 (OUTPUT); also elsewhere on the board
PLANE_8: JP8.1 (A), U12.2 (OUTPUT); also elsewhere on the board
XT0-4: JP13.2 (B), U14.2 (COM1); also elsewhere on the board
XT1-5: JP14.2 (B), U14.4 (COM2); also elsewhere on the board
XT2-6: JP15.2 (B), U14.9 (COM3); also elsewhere on the board
XT3-7: JP16.2 (B), U14.10 (COM4); also elsewhere on the board
YL0: JP9.2 (B), U13.2 (COM1); also elsewhere on the board
YL1: JP10.2 (B), U13.4 (COM2); also elsewhere on the board
YL2: JP11.2 (B), U13.9 (COM3); also elsewhere on the board
YL3: JP12.2 (B), U13.10 (COM4); also elsewhere on the board

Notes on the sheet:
HS4
SIMPLE ADD ONS see: https://hackaday.io/project/175182-simple-add-ons-sao
HS2
STEP 3: Install two quad switches and two decoupling caps.
STEP 5 (LOGIC BOARD): See instructions on Logic Board.
SILKSCREEN FRONT AND BACK: SAO, GNDD, 3V3, SDA,SCL GPIO1, GPIO2
NOTE: These GPIO will be used by Core Plane Select if that option is enabled.
[ALTERNATE] AMBIENT LIGHT SENSORS I2C 0x29
-OR-
[OPTIONAL] SAO #2 EXPANSION
If Hall Switches are inserted, keep the decoupling caps on the first sheet. If Hall Switches are used, they default to being connected to Plane5-8 wiring, without requiring any Solder Jumpers to be soldered. Recommended sensitivity ± (N and S) 3-7 mT (30-70 Gauss) (Toshiba TCS40DPR,LF is 4.4mT.)
HS1
STEP 4: Modify sense wire routing through connectors.
A PLACE FOR AIR WIRES IF YOU WANT TO USE THE INTERRUPT
HS3
STEP 1: Do NOT solder any JP9 through JP16.
STEP 2: Solder ONE plane JP1 to JP8.
[OPTIONAL] MULTI CORE PLANE SELECT
SILKSCREEN: ALS I2C 0x29
[ALTERNATE] HALL SWITCH ALTERNATES

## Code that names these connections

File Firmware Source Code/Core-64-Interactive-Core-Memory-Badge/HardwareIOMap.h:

/*
	PURPOSE: Define/assign/log the version scheme and number.
				Map out all of the IO for each version of the Core 64 hardware.
         		The Hardware_IO_Map.cpp file detects and sets the hardware version.
         		Specify firmware version manually in this file as a string.
	SETUP: Manually update the field assigned as VERSION


  	HARDWARE VERSION SCHEME (see https://semver.org/)
		Given a version number MAJOR.MINOR.PATCH, increment the:
			MAJOR version when you make incompatible API changes,
			MINOR version when you add functionality in a backwards compatible manner, and
			PATCH version when you make backwards compatible bug fixes.
	
	FIRMWARE VERSION SCHEME 
	    Same as hardware version scheme, with additional metadata extensions:
		    -DATE 		Example: -200101
						Two digit month, two digit day of the month
			.TIME 	    Example: |0800
						Time increments from build to build to clearly denote each unqiue iteration
*/

#ifndef HARDWARE_IO_MAP_H
#define HARDWARE_IO_MAP_H

#if (ARDUINO >= 100)
#include <Arduino.h>
#else
#include <WProgram.h>
#endif

#include <stdint.h>

#ifdef __cplusplus
extern "C" {
#endif

// #define SDCARD_ENABLE                  			// Program memory (6K) with Teensy LC
#define AMBIENT_LIGHT_SENSOR_LTR329_ENABLE   		// Program memory (14K) with Teensy LC
#define HALL_SENSOR_ENABLE							// Program memory (10K)
// #define HALL_SWITCH_ENABLE
#define NEON_PIXEL_ARRAY							// Serpentine, like Pimoroni Unicorn Hat
#define CORE64_LED_MATRIX							// Row Major, Progressive layout. Just like an array in C.
#define OLED_64X128
// #define OLED_128X128


void DetectHardwareVersion ();		// Use once to detect and set the hardware version variables.
/*
	****************************************** HARDWARE VERSION TABLE ******************************************
	| VERSION |  DATE      | DESCRIPTION                                                                       |
	------------------------------------------------------------------------------------------------------------
	| v0.1.0  | 2019-08-09 | Single board prototype development
	| v0.1.5  | 2020-02-22 | Single board, reworked board fixes, prototype development
	| v0.2.0  | 2020-03-16 | Single board, design updated to match v0.1.5, theoretically (not produced)
	| v0.3.0  | 2020-05-30 | Dual board, hardware version detection for 0.2.x (includes v0.1.x) and v0.3.x
	| v0.3.1  | 2020-05-30 | Two voltage regulators, 5V0 and 3V3, powered from common switch point
	| v0.4.0  | 2020-11-28 | Blue LB, Yellow CB with Plane 4 set, as-built bring-up
	| v0.5.0  | 2021-03-20 | Triple-board, Black LB/CB/CM
	------------------------------------------------------------------------------------------------------------
*/
	#define FIRMWAREVERSION "210425.1924"	// TO DO: Expand to be "0.4.0-210530.1340"
/*
	****************************************** FIRMWARE VERSION TABLE ******************************************
	| VERSION |  DATE      | DESCRIPTION                                                                       |
	------------------------------------------------------------------------------------------------------------
	| v0.1.0  | 2019-      | 
	| v0.1.5  | 2020-      | 
	| v0.2.0  | 2020-      | 
	| v0.3.x  | 2020-      | 
	| v0.4.x  | 2020-11-28 | 
	| v0.5.x  | 2021-03-20 | Accept V0.5.x hardware, manual default to the custom-fit LED Matrix.
	------------------------------------------------------------------------------------------------------------
*/
	extern uint8_t HardwareVersionMajor  ;
	extern uint8_t HardwareVersionMinor  ;
	extern uint8_t HardwareVersionPatch  ;

// HARDWARE v0.4.0
// MATRIX DRIVE
	#define PIN_MATRIX_DRIVE_Q1P     	 2	// * Shared
	#define PIN_MATRIX_DRIVE_Q1N     	 3
	#define PIN_MATRIX_DRIVE_Q2P     	 4	// * Shared
	#define PIN_MATRIX_DRIVE_Q2N     	 5	// * Shared
	#define PIN_MATRIX_DRIVE_Q3P     	 6	// * Shared
	#define PIN_MATRIX_DRIVE_Q3N     	 7
	#define PIN_MATRIX_DRIVE_Q4P     	 8	// * Shared
	#define PIN_MATRIX_DRIVE_Q4N     	 9	// * Shared
	#define PIN_MATRIX_DRIVE_Q5P     	16
	#define PIN_MATRIX_DRIVE_Q5N     	17
	#define PIN_MATRIX_DRIVE_Q6P     	24
	#define PIN_MATRIX_DRIVE_Q6N     	25
	#define PIN_MATRIX_DRIVE_Q7P     	26
	#define PIN_MATRIX_DRIVE_Q7N     	27   
	#define PIN_MATRIX_DRIVE_Q8P     	28   
	#define PIN_MATRIX_DRIVE_Q8N     	29   
	#define PIN_MATRIX_DRIVE_Q9P     	30
	#define PIN_MATRIX_DRIVE_Q9N     	31 
	#define PIN_MATRIX_DRIVE_Q10P    	32 
	#define PIN_MATRIX_DRIVE_Q10N    	33	
	#define PIN_WRITE_ENABLE         	23	// * Shared 
// MATRIX SENSE
	#define Pin_Sense_Reset         	21	// * Shared
	#define Pin_Sense_Pulse         	22	// * Shared
// LED ARRAY
	#define Pin_RGB_LED_Array           20	// * Shared 
// SPI
    #define Pin_SPI_OLED_CS				 2	// * Shared, digital output
    #define Pin_SPI_TOUCH_CS			 4	// * Shared, digital output
	#define Pin_SPI_SD_CS     		     6	// * Shared, digital output
    #define Pin_SPI_LCD_CS				 8	// * Shared, digital output
    #define Pin_SPI_LCD_DC				 9	// * Shared, digital output
    #define Pin_SPI_TeensyView_CS		10	// * Shared, digital output
    #define Pin_SPI_SDO					11  // Default Teensy
    #define Pin_SPI_SDI					12  // Default Teensy
	#define Pin_SPI_SD_CD     		    14	// * Shared, digital input and output
    #define Pin_SPI_CLK                 13	// * Shared, digital output
	#define Pin_SPI_Reset_Spare_5		15	// * Shared, digital output, multipurpose use, choose one #define below to uncomment and activate
		// #define Pin_SPARE_5_Assigned_To_Spare_5_Output
		#define Pin_SPARE_5_Assigned_To_Spare_5_Analog
    #define Pin_SPI_LCD_BACKLIGHT		20	// * Shared, digital output
	#define Pin_SPI_TeensyView_DC		21	// * Shared, digital output
	#define Pin_SPI_OLED_DC				23	// * Shared, digital output
// I2C
	#define Pin_I2C_Bus_Data         	18  // Default Teensy. #define not needed, as Wire.h library takes care of this pin configuration.
	#define Pin_I2C_Bus_Clock        	19  // Default Teensy. #define not needed, as Wire.h library takes care of this pin configuration.
// MISC
	#define Pin_SAO_G1_SPARE_1_CP_ADDR_0 0	// * Shared, multipurpose use, choose one #define below to uncomment and activate
		#define Pin_SAO_G1_SPARE_1_CP_ADDR_0_Assigned_To_CP_ADDR_0_Output
	#define Pin_SAO_G2_SPARE_2_CP_ADDR_1 1	// * Shared, multipurpose use, choose one #define below to uncomment and activate
		#define Pin_SAO_G2_SPARE_2_CP_ADDR_1_Assigned_To_CP_ADDR_1_Output
	#define Pin_IR_OUT					 5	// * Shared, digital output, multipurpose use, choose one #define below to uncomment and activate
    #define Pin_Spare_4_IR_IN			10	// * Shared
		#define Pin_Spare_4_IR_IN_Assigned_To_Spare_4_Output
	#define Pin_Built_In_LED         	13  // * Shared with SPI CLOCK
	//#define Pin_SPARE_3_CP_ADDR_2		14	// * Shared, multipurpose use, choose one #define below to uncomment and activate
		// #define Pin_SPARE_3_Assigned_To_Spare_3_Output
		// #define Pin_SPARE_3_CP_ADDR_2_Assigned_To_CP_ADDR_2_Output
		// #define Pin_SPARE_3_Assigned_To_Spare_3_Input
		// #define Pin_SPARE_3_Assigned_To_SPI_SD_CD_Input
		#define Pin_SPARE_3_Assigned_To_Spare_3_Analog_Input A0
	#define Pin_Battery_Voltage        A10  // 1/2 the battery voltage (otherwise known as Digital pin 24)
	#define Pin_SPARE_ANA_6			   A11
	#define Pin_SPARE_ANA_7			   A12
	#define Pin_SPARE_ANA_8			   A13
    #define Pin_Spare_ADC_DAC		   A14
    #ifdef HALL_SWITCH_ENABLE
		#define PIN_HALL_SWITCH_1		 1
		#define PIN_HALL_SWITCH_2		 2
		#define PIN_HALL_SWITCH_3		14
		#define PIN_HALL_SWITCH_4		10		
    #endif

#ifdef __cplusplus
} // extern "C"
#endif

#endif // HARDWARE_IO_MAP_H

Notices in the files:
parts and their libraries:
Copyright 2016 Accelerated Designs. All rights reserved.
